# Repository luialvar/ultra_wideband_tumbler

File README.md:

# Tumbler UWB Subsystem Workspace

This repository organizes the hardware, mechanical-design, power-analysis, embedded-driver, and firmware material for the Tumbler UWB node in the AMADEE-27 university robotics project. The software migration from the older SKITH/DWM1000 platform to a newer STM32L4/DWM3000 PCB is a central part of the work, but it is not the whole project: the repository also captures the PCB, mechanical-integration, power-budget, and bring-up context needed to make the Tumbler subsystem usable.

The project is intentionally split by layer. The legacy folders are kept as engineering references, while the new CubeMX firmware and the Tumbler PCB are the active migration target.

## Project Context: AMADEE-27

This work was developed in the context of a university robotics project preparing a contribution for AMADEE-27, an international Mars analog mission managed by the Austrian Space Forum (OeWF).

AMADEE-27 is designed to emulate selected aspects of a human-robotic Mars mission. The mission concept combines analog astronauts, robotic systems, field experiments, and a Mission Support Center in Austria to recreate operational constraints similar to planetary exploration. The official AMADEE-27 call focuses on areas such as engineering and robotics, planetary surface operations, geoscience, life sciences, and human factors.

Within that broader university project, my responsibility was the Tumbler UWB subsystem rather than only a code port. That included understanding the old UWB localization stack, contributing to mechanical design and integration ideas, helping around the new PCB by studying the schematic/layout and matching it to firmware pin names, learning the practical hardware constraints, documenting the PCB and power-budget context, and preparing the new STM32CubeMX/HAL firmware structure for the upgraded PCB.

External context:

- Austrian Space Forum AMADEE-27 overview: https://oewf.org/en/amadee-27/
- AMADEE-27 Announcement of Opportunity: https://oewf.org/en/2025/12/amadee-27-ao/

## Tumbler Subsystem Scope

The important object in this repository is the Tumbler UWB subsystem as an integrated robot component. In practice, that means the work spans several connected areas:

- mechanical design exploration for fitting the electronics into the Tumbler concept,
- support and learning around the new PCB design, including how schematic/layout choices become firmware pin definitions,
- power-budget tracking for tag and anchor operating assumptions,
- low-level STM32L4/DWM3000 bring-up,
- migration of the old UWB ranging ideas onto a new CubeMX/HAL and Qorvo DW3xxx base.

The firmware migration is therefore one part of a larger embedded-system integration effort.

## Migration Summary

| Layer | Legacy platform | New platform |
| --- | --- | --- |
| Hardware | DWM1000-based SKITH board | DWM3000-based Tumbler board |
| Microcontroller | STM32F407 | STM32L431 |
| Framework | RODOS and legacy board wrappers | STM32Cube HAL generated by CubeMX |
| UWB driver | Decawave DWM1000 API | Qorvo DW3xxx driver |
| Application | Legacy tag/anchor ranging code | New CubeMX firmware for the new PCB |

## Repository Map

| Folder | Purpose |
| --- | --- |
| `SKITH_old_PCB/` | Legacy PCB design for the old SKITH UWB node. It represents the old hardware side of the DWM1000/STM32F407 platform. |
| `Tumbler_new_PCB/` | New PCB design for the upgraded UWB node. It contains the KiCad project, schematic sheets, layout, 3D exports, and production outputs for the DWM3000/STM32L431 board. |
| `power_calculations/` | Spreadsheet-based power budgets. The files are grouped around the old and new PCB assumptions, including anchor/tag operating modes. |
| `old_uwb_reference_repo/` | Legacy university toolkit component used as a software reference. It contains the old embedded DWM1000 firmware plus robot-side ROS localization code. |
| `software_new_pcb/` | New STM32CubeMX/HAL firmware for the new PCB. This is the active new-board software area. |
| `tumbler_images/` | Mechanical concept images and visual material for the Tumbler integration work. |
| `useful_links.txt` | Extra project links and references collected during development. |

## What Is Reused

The useful software inheritance is at the protocol level, not at the low-level driver level. The legacy code is valuable because it already contains the tag/anchor ranging flow, message types, timestamp packing, and two-way-ranging state machine. Those concepts can be ported to the new firmware.

The old Decawave DWM1000 driver, the RODOS scheduling code, the old SPI/GPIO wrappers, and the old board calibration constants should not be copied directly into the new STM32L431/DWM3000 firmware.

## Current Engineering Focus

The new firmware is built around STM32Cube HAL and the Qorvo DW3xxx driver. CubeMX describes the real wiring from the new PCB, including SPI, IRQ, reset, wakeup, power-control, and BMS-related pins. The firmware then uses those generated names in the board-port layer so that the UWB driver can talk to the DWM3000 through the actual hardware connections.

The practical bring-up path is:

1. Validate the CubeMX pin map against the Tumbler PCB schematic.
2. Bring up SPI, reset, wakeup, chip-select, and IRQ in the STM32 port layer.
3. Read the DW3xxx device ID through the Qorvo driver.
4. Test raw TX/RX frames.
5. Port the old tag/anchor ranging logic onto the new driver and HAL base.
6. Recalibrate antenna delays and timing for the new board.

## Engineering Highlights

This repository demonstrates a full embedded migration across hardware, firmware, and tooling boundaries:

- connecting mechanical integration constraints with the electronics layout,
- helping translate the new PCB design into a firmware-facing pin map,
- translating real PCB wiring into CubeMX/HAL pin definitions,
- replacing a legacy DWM1000 driver stack with the Qorvo DW3xxx driver,
- separating reusable ranging logic from non-reusable board/framework code,
- keeping only the required DW3xxx driver sources inside the firmware tree instead of storing the full vendor SDK,
- connecting firmware operating modes to spreadsheet-based power estimates.

## Notes for Reviewers

This repository is a migration and integration workspace, so it intentionally contains both original references and new implementation work. The separation is important: hardware design files document the boards, the power spreadsheets document expected operating modes, and the CubeMX firmware is where the new embedded software and DW3xxx driver integration are implemented.

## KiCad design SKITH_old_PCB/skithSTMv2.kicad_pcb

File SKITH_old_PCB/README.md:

# SKITH Old PCB

This folder contains the legacy PCB design for the older SKITH UWB node used as the starting point of the migration.

In the overall project, this is the old hardware reference:

| Layer | Value |
| --- | --- |
| UWB module | DWM1000 |
| Microcontroller family | STM32F407 |
| Firmware stack used with this board | RODOS, legacy wrappers, Decawave DWM1000 API |
| Role in this repository | Hardware reference for the legacy platform |

## Contents

| File or folder | Purpose |
| --- | --- |
| `skithSTMv2.kicad_pro` | KiCad project entry point. Open this file in KiCad to inspect the board. |
| `skithSTMv2.kicad_pcb` | PCB layout. |
| `skithSTMv2.sch` | Legacy schematic file. |
| `Schaltplan_Skith_STM_2.pdf` | PDF schematic export for quick review. |
| `skithSTMv2.brd` | Board file from the older design flow. |
| `sym-lib-table` | KiCad symbol-library configuration. |
| `skithSTMv2.kicad_dru` | KiCad design-rule settings. |
| `skithSTMv2.kicad_prl` | KiCad local/session state; useful for KiCad, but not part of the engineering design itself. |

## How This Fits the Migration

This board is not the firmware target for the new implementation. It is included so the old DWM1000/STM32F407 hardware can be compared against the new DWM3000/STM32L431 design.

The old firmware associated with this hardware is kept separately in `../old_uwb_reference_repo/embedded_uwb/`. The PCB files here describe the electrical design: connectors, MCU pins, UWB module wiring, power rails, and board layout.

For the new board, see `../Tumbler_new_PCB/`.

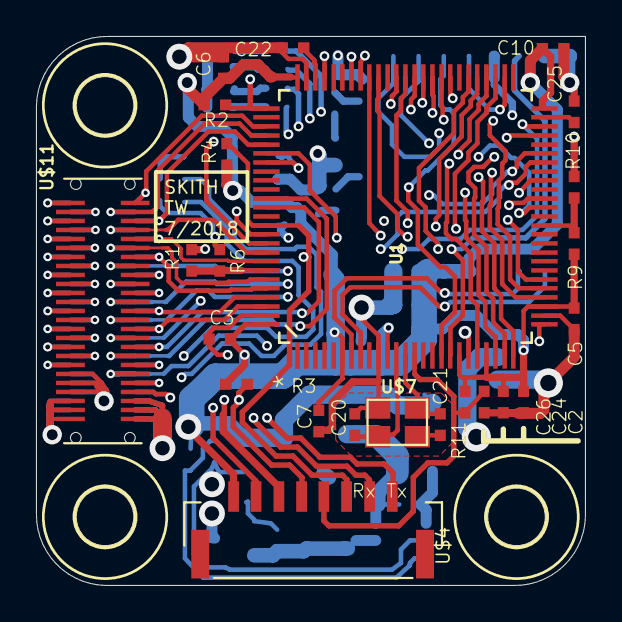
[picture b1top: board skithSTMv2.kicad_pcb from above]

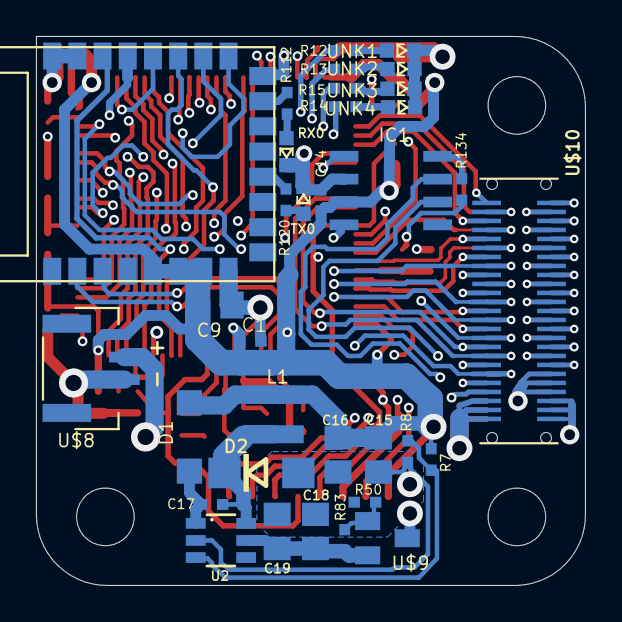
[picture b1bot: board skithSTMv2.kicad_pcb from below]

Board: 4 copper layers, 30.5 x 30.5 mm, 61 parts (34 on the bottom side), 79 nets.

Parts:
C1, C2, C3, C5, C6, C7, C10, C14, C17, C24, C26: 100n; C0402
C9, C15, C16, C18, C19: 10µ; C0805
C20, C21: 22p; C0402
C22, C25: 2,2µ; C0402
D1: 1N4148W-7-F; SOD123
D2: DO214AC
IC1: SN65HVD231D; SO8
L1: WE-TPC_2828
R1, R2, R3, R4, R6, R8, R9, R10, R11: 10k; R0402
R7: 31,6K; R0402
R12, R13, R14, R15, R112, R120, R134: 270; R0402
R50, R83: 1Meg; R0402
RX0: grün; SML0603
TX0: rot; SML0603
U1: STM32F407VGT6; QFP50P1600X1600X160-100N
U2: MCP16331; SOT23-6
U$1, U$5, U$6: 3,2
U$3: DWM1000
U$4: SM08B-GHS-TB
U$7: QC3CA16.0000F12B23M; LFXTAL055998
U$8: SM02B-GHS-TB
U$9: SI2369DS-T1-GE3; SOT23
U$10: DF12A-50DS-0.5V
U$11: DF12D(5.0)-50DP-0.5V
UNK1: grün; SML0603
UNK2: gelb; SML0603
UNK3: rot; SML0603
UNK4: blau; SML0603

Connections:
+3V3: C1.1, C2.1, C3.1, C5.1, C6.1, C7.1, C9.1, C10.1, C14.2, C15.1, C16.1, C24.1, D1.A, IC1.3, L1.2, R1.2, R2.2, R3.2, R4.1, R7.2, R9.2, R11.2, U1.6, U1.11, U1.19, U1.22, U1.28, U1.50, U1.75, U1.100, U$3.5, U$3.6, U$3.7, U$4.1, U$10.20, U$10.21, U$10.22, U$11.20, U$11.21, U$11.22
+24V: C18.1, C19.1, R83.2, U2.5, U$9.2
AD0: U1.23, U$10.8, U$11.8
AD1: U1.24, U$10.7, U$11.7
AD2: U1.25, U$10.6, U$11.6
AD3: U1.26, U$10.5, U$11.5
AD4: U1.29, U$10.4, U$11.4
AD5: U1.30, U$10.1, U$11.1
AD_REF: U1.21, U$10.2, U$11.2
BOOT1: R9.1, R10.2, U1.37
CAN1_RX: IC1.4, U1.81
CAN1_TX: IC1.1, U1.82
CAN_H: IC1.7, U$10.15, U$11.15
CAN_L: IC1.6, U$10.16, U$11.16
DEBUG_UART_RX: U1.69, U$4.7
DEBUG_UART_TX: U1.68, U$4.8
GND: C1.2, C2.2, C3.2, C5.2, C6.2, C7.2, C9.2, C10.2, C14.1, C15.2, C16.2, C18.2, C19.2, C20.2, C21.2, C22.2, C24.2, C25.2, C26.1, D2.A, IC1.2, R6.1, R8.1, R10.1, R50.1, R134.2, RX0.C, TX0.C, U1.10, U1.20, U1.27, U1.74, U1.99, U2.2, U$3.8, U$3.16, U$3.21, U$3.23, U$3.24, U$4.3, U$7.2, U$7.4, U$8.2, U$10.3, U$10.18, U$10.19, U$10.23, U$10.24, U$10.25, U$11.3, U$11.18, U$11.19, U$11.23, U$11.24, U$11.25, UNK1.C, UNK2.C, UNK3.C, UNK4.C
I2C_SCL: U1.47, U$10.17, U$11.17
I2C_SDA: U1.48, U$10.35, U$11.35
JTCK: R2.1, U1.76, U$4.2
JTMS: R3.1, U1.72, U$4.4
LED_BLAU: R12.2, U1.62
LED_GELB: R15.2, U1.60
LED_GRUEN: R14.2, U1.59
LED_ROT: R13.2, U1.61
unnamed: C22.1, U1.73
unnamed: R112.2, U$3.15
unnamed: R7.1, R8.2, U2.3
unnamed: C17.1, D1.C, U2.1
unnamed: C17.2, D2.C, L1.1, U2.6
unnamed: R12.1, UNK1.A
unnamed: R13.1, UNK2.A
unnamed: R14.1, UNK4.A
unnamed: R1.1, R6.2, U1.94
unnamed: R15.1, UNK3.A
unnamed: C25.1, U1.49
unnamed: IC1.8, R134.1
unnamed: R112.1, RX0.A
unnamed: R120.1, TX0.A
unnamed: R120.2, U$3.12
unnamed: R50.2, R83.1, U$9.1
NRST: C26.2, R11.1, U1.14, U$4.5
P0: U1.78, U$10.50, U$11.50
P1: U1.79, U$10.49, U$11.49
P2: U1.80, U$10.48, U$11.48
P3: U1.92, U$10.47, U$11.47
P4: U1.93, U$10.46, U$11.46
P5: U1.95, U$10.45, U$11.45
P6: U1.96, U$10.44, U$11.44
P7: U1.67, U$10.43, U$11.43
P8: U1.63, U$10.37, U$11.37
P9: U1.98, U$10.36, U$11.36
PH0: C20.1, U1.12, U$7.1
PH1: C21.1, U1.13, U$7.3
PWM0: U1.40, U$10.40, U$11.40
PWM1: U1.42, U$10.41, U$11.41
PWM2: U1.44, U$10.39, U$11.39
PWM3: U1.45, U$10.42, U$11.42
SPI0_CS0: U1.31, U$10.13, U$11.13
SPI0_CS1: U1.66, U$10.14, U$11.14
SPI0_CS2: U1.64, U$10.9, U$11.9
SPI0_CS3: U1.97, U$10.38, U$11.38
SPI0_MISO: U1.90, U$10.10, U$11.10
SPI0_MOSI: U1.91, U$10.11, U$11.11
SPI0_SCK/SWO: R4.2, U1.89, U$4.6, U$10.12, U$11.12
SPI_CS_DWM1000: U1.39, U$3.17
SPI_MISO_DWM1000: U1.17, U$3.19
SPI_MOSI_DWM1000: U1.54, U$3.18
SPI_SCK_DWM1000: U1.52, U$3.20
UART0_RX: U1.87, U$10.34, U$11.34
UART0_TX: U1.86, U$10.33, U$11.33
UART1_CTS: U1.58, U$10.29, U$11.29
UART1_RTS: U1.53, U$10.30, U$11.30
UART1_RX: U1.56, U$10.32, U$11.32
UART1_TX: U1.55, U$10.31, U$11.31
UWB_INT: U1.18, U$3.22
UWB_RESET: U1.7, U$3.3
UWB_WAKEUP: U1.8, U$3.2
V+: U$8.1, U$9.3, U$10.26, U$10.27, U$10.28, U$11.26, U$11.27, U$11.28

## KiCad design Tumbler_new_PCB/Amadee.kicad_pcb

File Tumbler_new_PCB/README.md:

# Tumbler New PCB

This folder contains the new PCB design for the upgraded UWB node. It is the hardware target for the STM32CubeMX/HAL firmware in `../software_new_pcb/`.

In the overall migration, this is the new hardware platform:

| Layer | Value |
| --- | --- |
| UWB module | DWM3000 family |
| Microcontroller | STM32L431 |
| Firmware stack | STM32Cube HAL plus Qorvo DW3xxx driver |
| Role in this repository | Active hardware target for the new firmware |

## Contents

| File or folder | Purpose |
| --- | --- |
| `Amadee.kicad_pro` | Main KiCad project entry point. Open this file first in KiCad. |
| `Amadee.kicad_sch` | Top-level schematic. |
| `mcu.kicad_sch` | Microcontroller schematic sheet. |
| `B2Bconn.kicad_sch` | Board-to-board connector sheet. |
| `bms.kicad_sch` | Battery-management subsystem sheet. |
| `buck.kicad_sch` | Buck-regulator/power-conversion sheet. |
| `usb.kicad_sch` | USB-related circuitry. |
| `back-to-back-fets.kicad_sch` | Power-path/protection FET sheet. |
| `Amadee.kicad_pcb` | PCB layout. |
| `AmadeeTumbler.step` | 3D mechanical export for CAD review. |
| `AmadeeTumbler.stl` | 3D mesh export. |
| `AmadeeTumbler.pdf` | PDF design export for quick review. |
| `production/` | Manufacturing outputs. |
| `PowerCalc/` | Power-calculation spreadsheets colocated with the PCB project. |
| `lib/` | KiCad footprint/library assets used by the board. |

## Firmware-Relevant Signals

The PCB defines the real electrical wiring. CubeMX must mirror that wiring so the firmware can use the correct MCU pins for:

| Signal group | Why it matters in firmware |
| --- | --- |
| SPI | Data path between the STM32L431 and the DWM3000. |
| Chip select | Selects the UWB chip during SPI transactions. |
| IRQ | Lets the DWM3000 notify the MCU about TX/RX events. |
| Reset | Allows the MCU to reset the UWB module during bring-up. |
| Wakeup | Lets the MCU bring the UWB module out of low-power states. |
| Power and BMS pins | Control and monitor board power behavior. |

This is why the PCB and CubeMX project must agree. The PCB is the physical truth; CubeMX translates that physical wiring into generated C names used by the HAL and by the Qorvo driver port layer.

## Relationship to the Old PCB

The old `../SKITH_old_PCB/` design represents the DWM1000/STM32F407 generation. This folder represents the DWM3000/STM32L431 generation.

The migration is therefore not just a source-code copy. It changes the radio module, the MCU, the framework, the low-level driver, and the board pinout.

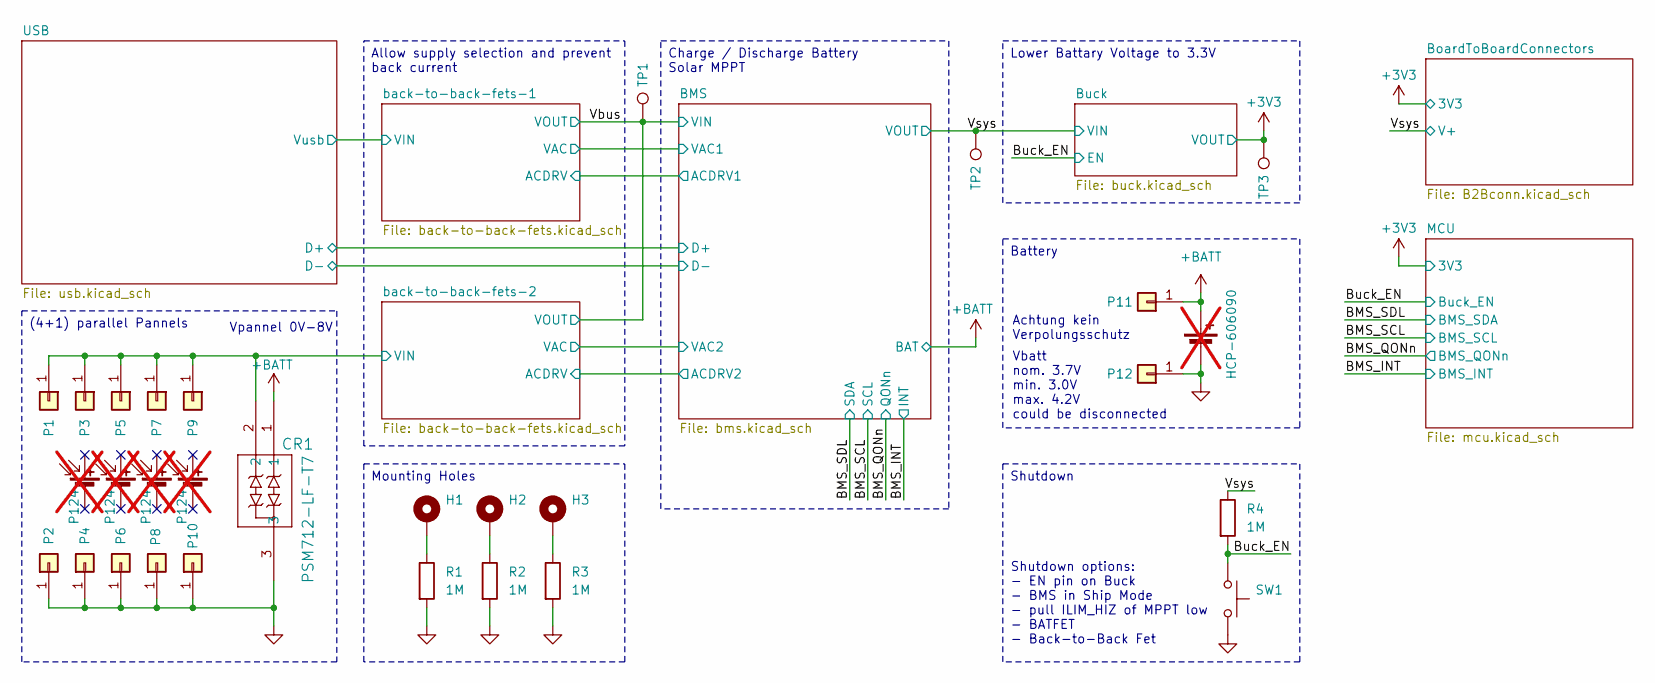
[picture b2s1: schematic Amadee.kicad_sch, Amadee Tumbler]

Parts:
BT1: HCP-606090; not fitted
CR1: PSM712-LF-T7; CR_SOT-23_PTD; LCSC C32677
H1, H2, H3: MountingHole_Pad; MountingHole_3.2mm_M3_DIN965_Pad
P1, P2, P3, P4, P5, P6, P7, P8, P9, P10, P11, P12: SolderPad_4mm_2mm
R1, R2, R3: 1M; R_0603_1608Metric_Pad0.98x0.95mm_HandSolder
R4: 1M; R_0402_1005Metric_Pad0.72x0.64mm_HandSolder
SC1, SC2, SC3, SC4: P124; not fitted
SW1: SW_Push; SW_SPST_TS-1088-xR020; LCSC C720477
TP1, TP2, TP3: TestPoint; TestPoint_Pad_D1.5mm

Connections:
+3V3: TP3.1 (1_1); also elsewhere on the board
+BATT: BT1.1 (+), CR1.1, P11.1 (Pin_1_1); also elsewhere on the board
/BMS/VAC2: CR1.2, P1.1 (Pin_1_1), P3.1 (Pin_1_1), P5.1 (Pin_1_1), P7.1 (Pin_1_1), P9.1 (Pin_1_1); also elsewhere on the board
/Buck_EN: R4.2, SW1.1; also elsewhere on the board
/Vbus: TP1.1 (1_1); also elsewhere on the board
/Vsys: R4.1, TP2.1 (1_1); also elsewhere on the board
GND: BT1.2 (-), CR1.3, P2.1 (Pin_1_1), P4.1 (Pin_1_1), P6.1 (Pin_1_1), P8.1 (Pin_1_1), P10.1 (Pin_1_1), P12.1 (Pin_1_1), R1.2, R2.2, R3.2, SW1.2; also elsewhere on the board
unnamed: H1.1 (1_1), R1.1
unnamed: H2.1 (1_1), R2.1
unnamed: H3.1 (1_1), R3.1

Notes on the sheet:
Vpannel 0V-8V
Vbatt nom. 3.7V min. 3.0V max. 4.2V could be disconnected
Shutdown options: - EN pin on Buck - BMS in Ship Mode - pull ILIM_HIZ of MPPT low - BATFET - Back-to-Back Fet
Achtung kein Verpolungsschutz
Battery
Lower Battary Voltage to 3.3V
Charge / Discharge Battery Solar MPPT
Shutdown
Allow supply selection and prevent back current
(4+1) parallel Pannels
Mounting Holes

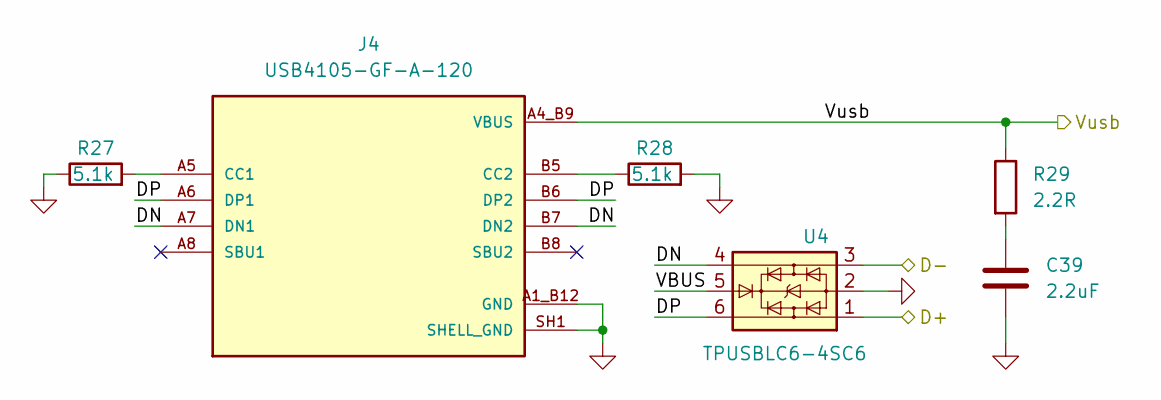
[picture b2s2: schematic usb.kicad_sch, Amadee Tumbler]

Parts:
C39: 2.2uF; C_0805_2012Metric_Pad1.18x1.45mm_HandSolder
J4: USB4105-GF-A-120; GCT_USB4105-GF-A-120; PARTREV B3; LCSC C5184243
R27, R28: 5.1k; R_0603_1608Metric_Pad0.98x0.95mm_HandSolder
R29: 2.2R; R_0603_1608Metric_Pad0.98x0.95mm_HandSolder
U4: TPUSBLC6-4SC6; SOT-23-6; LCSC C558419

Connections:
/BMS/D+: U4.1; also elsewhere on the board
/BMS/D-: U4.3; also elsewhere on the board
/USB/DN: J4.A7 (DN1), J4.B7 (DN2), U4.4
/USB/DP: J4.A6 (DP1), J4.B6 (DP2), U4.6
GND: C39.2, J4.A1_B12 (GND), J4.B1_A12 (GND), J4.SH1 (SHELL_GND), J4.SH2 (SHELL_GND), J4.SH3 (SHELL_GND), J4.SH4 (SHELL_GND), R27.1, R28.2, U4.2; also elsewhere on the board
unnamed: C39.1, R29.2
unnamed: J4.A5 (CC1), R27.2
unnamed: J4.B5 (CC2), R28.1
VBUS: J4.A4_B9 (VBUS), J4.B4_A9 (VBUS), R29.1, U4.5; also elsewhere on the board

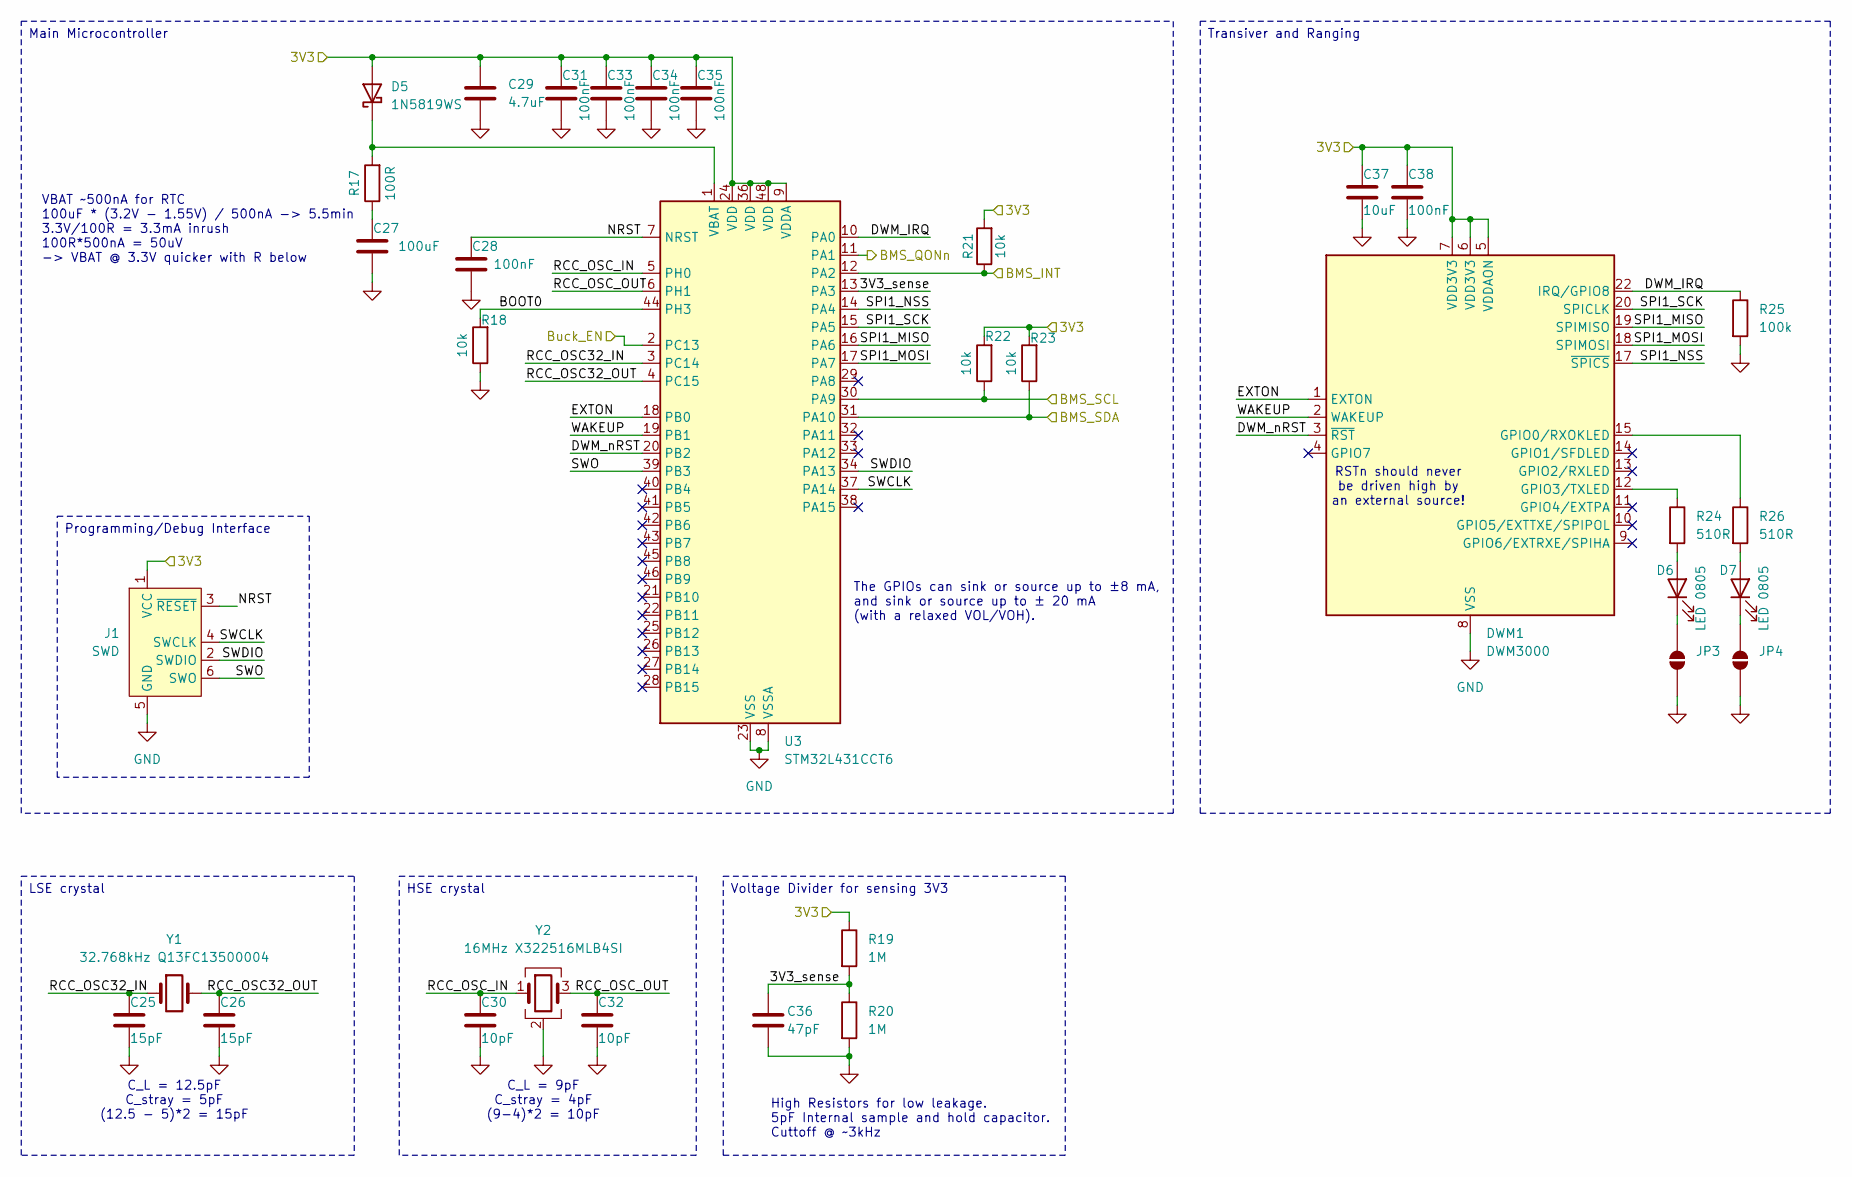
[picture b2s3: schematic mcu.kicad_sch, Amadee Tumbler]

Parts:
C25, C26: 15pF; C_0402_1005Metric
C27: 100uF; C_1206_3216Metric
C28, C31, C33, C34, C35, C38: 100nF; C_0402_1005Metric_Pad0.74x0.62mm_HandSolder
C29: 4.7uF; C_0805_2012Metric_Pad1.18x1.45mm_HandSolder
C30, C32: 10pF; C_0402_1005Metric
C36: 47pF; C_0402_1005Metric_Pad0.74x0.62mm_HandSolder
C37: 10uF; C_0402_1005Metric_Pad0.74x0.62mm_HandSolder
D5: 1N5819WS; D_SOD-323
D6, D7: LED 0805; LED_0805_2012Metric_Pad1.15x1.40mm_HandSolder; LCSC C2296
DWM1: DWM3000; DWM1000; LCSC C42419011
J1: SWD; PinHeader_2x03_P2.54mm_Vertical_SMD; LCSC C192301
JP3, JP4: SolderJumper_2_Open; SolderJumper-2_P1.3mm_Open_RoundedPad1.0x1.5mm
R17: 100R; R_0402_1005Metric_Pad0.72x0.64mm_HandSolder
R18, R21, R22, R23: 10k; R_0402_1005Metric_Pad0.72x0.64mm_HandSolder
R19, R20: 1M; R_0402_1005Metric_Pad0.72x0.64mm_HandSolder
R24, R26: 510R; R_0402_1005Metric_Pad0.72x0.64mm_HandSolder
R25: 100k; R_0402_1005Metric_Pad0.72x0.64mm_HandSolder
U3: STM32L431CCT6; LQFP-48_7x7mm_P0.5mm; LCSC C486681
Y1: 32.768kHz Q13FC13500004; Crystal_SMD_3215-2Pin_3.2x1.5mm; LCSC C32346
Y2: 16MHz X322516MLB4SI; Crystal_SMD_3225-4Pin_3.2x2.5mm; LCSC C13738

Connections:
+3V3: C29.1, C31.1, C33.1, C34.1, C35.1, C37.1, C38.1, D5.2 (A), DWM1.5 (VDDAON), DWM1.6 (VDD3V3), DWM1.7 (VDD3V3), J1.1 (VCC), R19.1, R21.2, R22.2, R23.2, U3.9 (VDDA), U3.24 (VDD), U3.36 (VDD), U3.48 (VDD); also elsewhere on the board
/BMS_INT: R21.1, U3.12 (PA2); also elsewhere on the board
/BMS_QONn: U3.11 (PA1); also elsewhere on the board
/BMS_SCL: R22.1, U3.30 (PA9); also elsewhere on the board
/BMS_SDL: R23.1, U3.31 (PA10); also elsewhere on the board
/Buck_EN: U3.2 (PC13); also elsewhere on the board
/MCU/3V3_sense: C36.1, R19.2, R20.1, U3.13 (PA3)
/MCU/BOOT0: R18.2, U3.44 (PH3)
/MCU/DWM_IRQ: DWM1.22 (IRQ/GPIO8), R25.1, U3.10 (PA0)
/MCU/DWM_nRST: DWM1.3 (~RST), U3.20 (PB2)
/MCU/EXTON: DWM1.1 (EXTON), U3.18 (PB0)
/MCU/NRST: C28.1, J1.3 (~RESET), U3.7 (NRST)
/MCU/RCC_OSC32_IN: C25.1, U3.3 (PC14), Y1.1
/MCU/RCC_OSC32_OUT: C26.1, U3.4 (PC15), Y1.2
/MCU/RCC_OSC_IN: C30.1, U3.5 (PH0), Y2.1
/MCU/RCC_OSC_OUT: C32.1, U3.6 (PH1), Y2.3
/MCU/SPI1_MISO: DWM1.19 (SPIMISO), U3.16 (PA6)
/MCU/SPI1_MOSI: DWM1.18 (SPIMOSI), U3.17 (PA7)
/MCU/SPI1_NSS: DWM1.17 (~SPICS), U3.14 (PA4)
/MCU/SPI1_SCK: DWM1.20 (SPICLK), U3.15 (PA5)
/MCU/SWCLK: J1.4 (SWCLK), U3.37 (PA14)
/MCU/SWDIO: J1.2 (SWDIO), U3.34 (PA13)
/MCU/SWO: J1.6 (SWO), U3.39 (PB3)
/MCU/WAKEUP: DWM1.2 (WAKEUP), U3.19 (PB1)
GND: C25.2, C26.2, C27.2, C28.2, C29.2, C30.2, C31.2, C32.2, C33.2, C34.2, C35.2, C36.2, C37.2, C38.2, DWM1.8 (VSS), DWM1.16 (VSS), DWM1.21 (VSS), DWM1.23 (VSS), DWM1.24 (VSS), J1.5 (GND), JP3.1 (A), JP4.1 (A), R18.1, R20.2, R25.2, U3.8 (VSSA), U3.23 (VSS), U3.35 (VSS), U3.47 (VSS), Y2.2 (G), Y2.4 (G); also elsewhere on the board
unnamed: C27.1, R17.1
unnamed: D5.1 (K), R17.2, U3.1 (VBAT)
unnamed: D6.2 (A), R24.2
unnamed: D6.1 (K), JP3.2 (B)
unnamed: D7.2 (A), R26.2
unnamed: D7.1 (K), JP4.2 (B)
unnamed: DWM1.15 (GPIO0/RXOKLED), R26.1
unnamed: DWM1.12 (GPIO3/TXLED), R24.1

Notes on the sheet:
VBAT ~500nA for RTC 100uF * (3.2V - 1.55V) / 500nA -> 5.5min 3.3V/100R = 3.3mA inrush 100R*500nA = 50uV -> VBAT @ 3.3V quicker with R below
The GPIOs can sink or source up to ±8 mA, and sink or source up to ± 20 mA (with a relaxed VOL/VOH).
C_L = 12.5pF C_stray = 5pF (12.5 - 5)*2 = 15pF
C_L = 9pF C_stray = 4pF (9-4)*2 = 10pF
High Resistors for low leakage. 5pF Internal sample and hold capacitor. Cuttoff @ ~3kHz
RSTn should never be driven high by an external source!
HSE crystal
Voltage Divider for sensing 3V3
Transiver and Ranging
LSE crystal
Main Microcontroller
Programming/Debug Interface

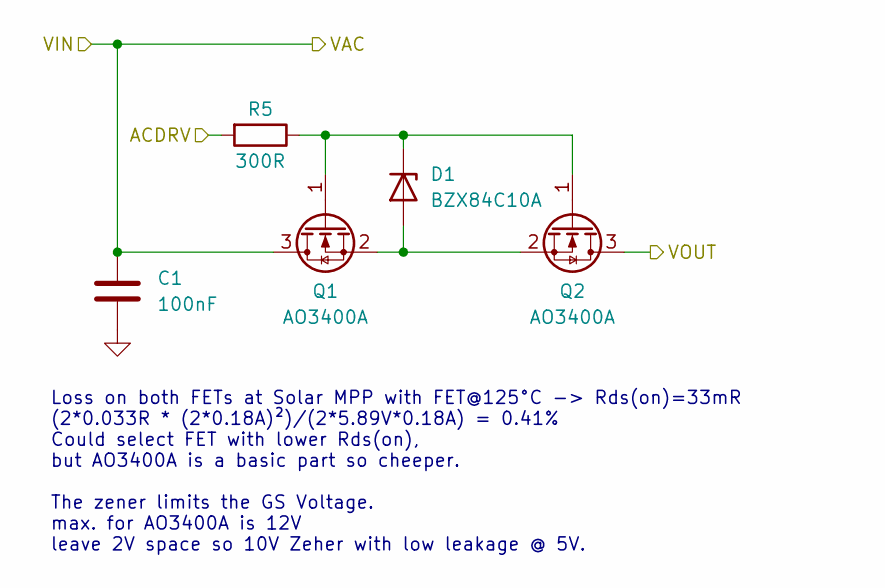
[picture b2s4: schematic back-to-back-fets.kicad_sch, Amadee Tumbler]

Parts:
C1: 100nF; C_0402_1005Metric_Pad0.74x0.62mm_HandSolder
D1: BZX84C10A; SOT-23; LCSC C5155278
Q1, Q2: AO3400A; SOT-23; LCSC C20917
R5: 300R; R_0402_1005Metric_Pad0.72x0.64mm_HandSolder

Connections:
/BMS/ACDRV1: R5.2; also elsewhere on the board
/Vbus: Q2.3 (D); also elsewhere on the board
GND: C1.2; also elsewhere on the board
unnamed: D1.1 (A), Q1.2 (S), Q2.2 (S)
unnamed: D1.3 (K), Q1.1 (G), Q2.1 (G), R5.1
VBUS: C1.1, Q1.3 (D); also elsewhere on the board

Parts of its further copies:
C2: 100nF; C_0402_1005Metric_Pad0.74x0.62mm_HandSolder
D2: BZX84C10A; SOT-23; LCSC C5155278
Q3, Q4: AO3400A; SOT-23; LCSC C20917
R6: 300R; R_0402_1005Metric_Pad0.72x0.64mm_HandSolder

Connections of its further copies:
/BMS/ACDRV2: R6.2; also elsewhere on the board
/BMS/VAC2: C2.1, Q3.3 (D); also elsewhere on the board
/Vbus: Q4.3 (D); also elsewhere on the board
GND: C2.2; also elsewhere on the board
unnamed: D2.1 (A), Q3.2 (S), Q4.2 (S)
unnamed: D2.3 (K), Q3.1 (G), Q4.1 (G), R6.1

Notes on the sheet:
Loss on both FETs at Solar MPP with FET@125°C -> Rds(on)=33mR (2*0.033R * (2*0.18A)²)/(2*5.89V*0.18A) = 0.41% Could select FET with lower Rds(on), but AO3400A is a basic part so cheeper. The zener limits the GS Voltage. max. for AO3400A is 12V leave 2V space so 10V Zeher with low leakage @ 5V.

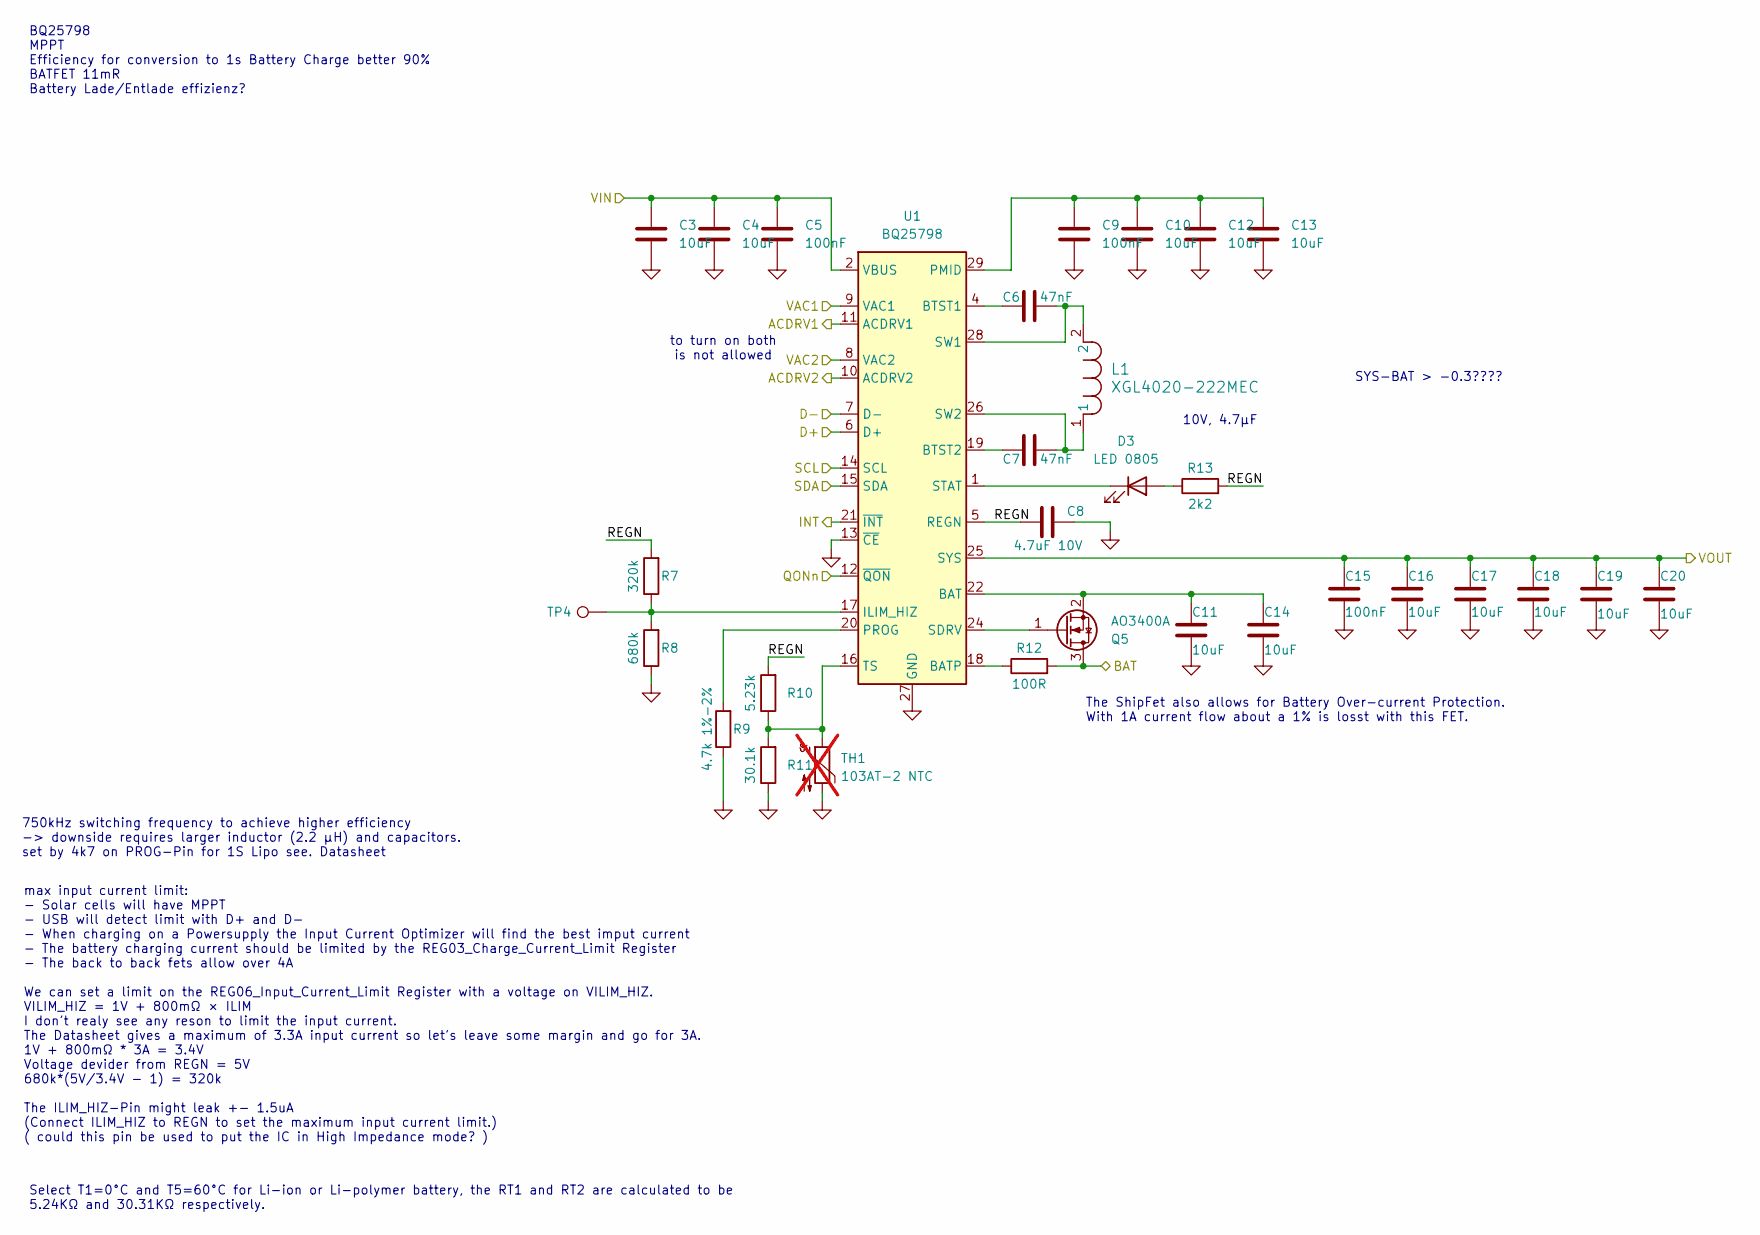
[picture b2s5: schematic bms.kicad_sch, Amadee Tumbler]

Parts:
C3, C4, C10, C11, C12, C13, C14, C16, C17, C18, C19, C20: 10uF; C_0402_1005Metric_Pad0.74x0.62mm_HandSolder
C5, C9, C15: 100nF; C_0402_1005Metric_Pad0.74x0.62mm_HandSolder
C6, C7: 47nF; C_0402_1005Metric_Pad0.74x0.62mm_HandSolder
C8: 4.7uF 10V; C_0402_1005Metric_Pad0.74x0.62mm_HandSolder
D3: LED 0805; LED_0805_2012Metric_Pad1.15x1.40mm_HandSolder; LCSC C2296
L1: XGL4020-222MEC; IND_XGL4020_COC
Q5: AO3400A; SOT-23; LCSC C20917
R7: 320k; R_0402_1005Metric_Pad0.72x0.64mm_HandSolder
R8: 680k; R_0402_1005Metric_Pad0.72x0.64mm_HandSolder
R9: 4.7k 1%-2%; R_0402_1005Metric_Pad0.72x0.64mm_HandSolder
R10: 5.23k; R_0402_1005Metric_Pad0.72x0.64mm_HandSolder
R11: 30.1k; R_0402_1005Metric_Pad0.72x0.64mm_HandSolder
R12: 100R; R_0402_1005Metric_Pad0.72x0.64mm_HandSolder
R13: 2k2; R_0402_1005Metric_Pad0.72x0.64mm_HandSolder
TH1: 103AT-2 NTC; PinHeader_1x02_P2.54mm_Vertical; not fitted
TP4: TestPoint; TestPoint_Pad_D1.0mm
U1: BQ25798; Texas_RQM0029A_VQFN-29_4x4mm_P0.4mm

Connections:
+BATT: Q5.3 (D), R12.2; also elsewhere on the board
/BMS/ACDRV1: U1.11 (ACDRV1); also elsewhere on the board
/BMS/ACDRV2: U1.10 (ACDRV2); also elsewhere on the board
/BMS/D+: U1.6 (D+); also elsewhere on the board
/BMS/D-: U1.7 (D-); also elsewhere on the board
/BMS/REGN: C8.1, R7.2, R10.2, R13.2, U1.5 (REGN)
/BMS/VAC2: U1.8 (VAC2); also elsewhere on the board
/BMS_INT: U1.21 (~INT); also elsewhere on the board
/BMS_QONn: U1.12 (~QON); also elsewhere on the board
/BMS_SCL: U1.14 (SCL); also elsewhere on the board
/BMS_SDL: U1.15 (SDA); also elsewhere on the board
/Vbus: C3.1, C4.1, C5.1, U1.2 (VBUS), U1.3 (VBUS); also elsewhere on the board
/Vsys: C15.1, C16.1, C17.1, C18.1, C19.1, C20.1, U1.25 (SYS); also elsewhere on the board
GND: C3.2, C4.2, C5.2, C8.2, C9.2, C10.2, C11.2, C12.2, C13.2, C14.2, C15.2, C16.2, C17.2, C18.2, C19.2, C20.2, R8.1, R9.1, R11.1, TH1.2, U1.13 (~CE), U1.27 (GND); also elsewhere on the board
unnamed: D3.2 (A), R13.1
unnamed: D3.1 (K), U1.1 (STAT)
unnamed: Q5.1 (G), U1.24 (SDRV)
unnamed: C11.1, C14.1, Q5.2 (S), U1.22 (BAT), U1.23 (BAT)
unnamed: R12.1, U1.18 (BATP)
unnamed: C6.1, U1.4 (BTST1)
unnamed: C7.1, U1.19 (BTST2)
unnamed: R7.1, R8.2, TP4.1 (1_1), U1.17 (ILIM_HIZ)
unnamed: C9.1, C10.1, C12.1, C13.1, U1.29 (PMID)
unnamed: R9.2, U1.20 (PROG)
unnamed: C6.2, L1.2, U1.28 (SW1)
unnamed: C7.2, L1.1, U1.26 (SW2)
unnamed: R10.1, R11.2, TH1.1, U1.16 (TS)
VBUS: U1.9 (VAC1); also elsewhere on the board

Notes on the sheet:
SYS-BAT > -0.3????
The ShipFet also allows for Battery Over-current Protection. With 1A current flow about a 1% is losst with this FET.
max input current limit: - Solar cells will have MPPT - USB will detect limit with D+ and D- - When charging on a Powersupply the Input Current Optimizer will find the best imput current - The battery charging current should be limited by the REG03_Charge_Current_Limit Register - The back to back f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
BQ25798 MPPT Efficiency for conversion to 1s Battery Charge better 90% BATFET 11mR Battery Lade/Entlade effizienz?
10V, 4.7μF
Select T1=0°C and T5=60°C for Li-ion or Li-polymer battery, the RT1 and RT2 are calculated to be 5.24KΩ and 30.31KΩ respectively.
750kHz switching frequency to achieve higher efficiency -> downside requires larger inductor (2.2 μH) and capacitors. set by 4k7 on PROG-Pin for 1S Lipo see. Datasheet
to turn on both is not allowed

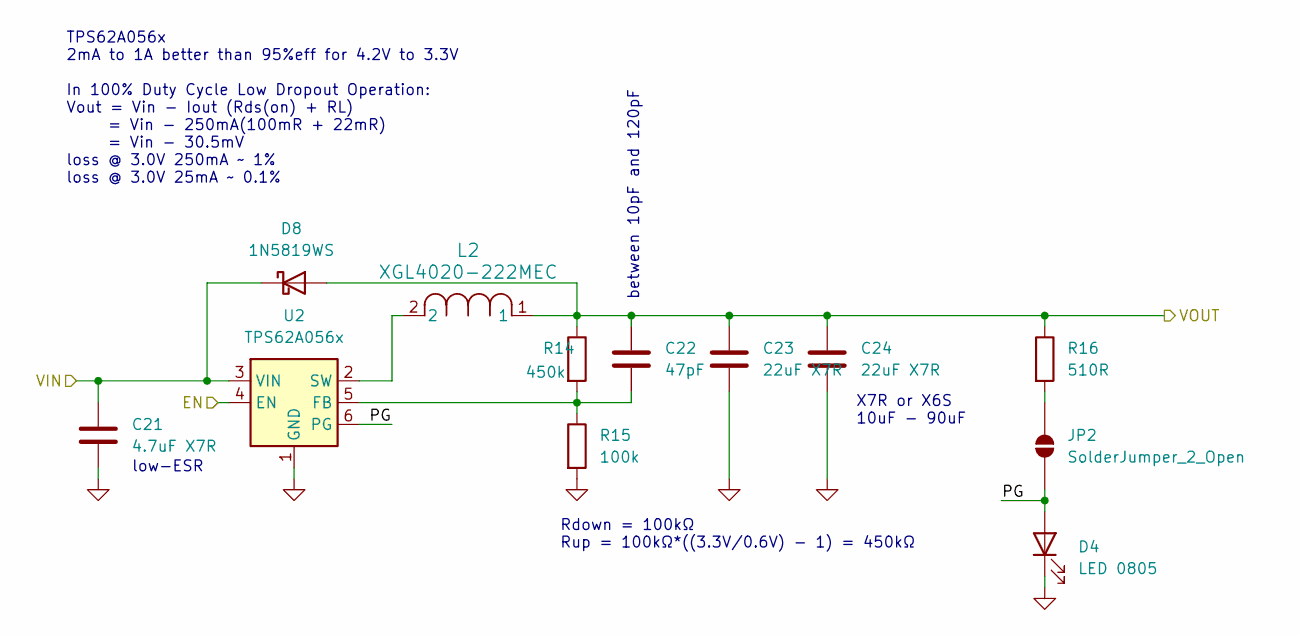
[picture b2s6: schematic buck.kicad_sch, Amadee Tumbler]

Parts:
C21: 4.7uF X7R; C_0805_2012Metric_Pad1.18x1.45mm_HandSolder; LCSC C49678
C22: 47pF; C_0402_1005Metric_Pad0.74x0.62mm_HandSolder
C23, C24: 22uF X7R; C_0805_2012Metric_Pad1.18x1.45mm_HandSolder
D4: LED 0805; LED_0805_2012Metric_Pad1.15x1.40mm_HandSolder; LCSC C2296
D8: 1N5819WS; D_SOD-323
JP2: SolderJumper_2_Open; SolderJumper-2_P1.3mm_Open_RoundedPad1.0x1.5mm
L2: XGL4020-222MEC; IND_XGL4020_COC
R14: 450k; R_0402_1005Metric_Pad0.72x0.64mm_HandSolder
R15: 100k; R_0402_1005Metric_Pad0.72x0.64mm_HandSolder
R16: 510R; R_0402_1005Metric_Pad0.72x0.64mm_HandSolder
U2: TPS62A056x; SOT-563

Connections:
+3V3: C22.1, C23.1, C24.1, D8.2 (A), L2.1, R14.1, R16.1; also elsewhere on the board
/Buck/PG: D4.2 (A), JP2.1 (A), U2.6 (PG)
/Buck_EN: U2.4 (EN); also elsewhere on the board
/Vsys: C21.1, D8.1 (K), U2.3 (VIN); also elsewhere on the board
GND: C21.2, C23.2, C24.2, D4.1 (K), R15.2, U2.1 (GND); also elsewhere on the board
unnamed: JP2.2 (B), R16.2
unnamed: C22.2, R14.2, R15.1, U2.5 (FB)
unnamed: L2.2, U2.2 (SW)

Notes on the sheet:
Rdown = 100kΩ Rup = 100kΩ*((3.3V/0.6V) - 1) = 450kΩ
low-ESR
TPS62A056x 2mA to 1A better than 95%eff for 4.2V to 3.3V In 100% Duty Cycle Low Dropout Operation: Vout = Vin - Iout (Rds(on) + RL) = Vin - 250mA(100mR + 22mR) = Vin - 30.5mV loss @ 3.0V 250mA ~ 1% loss @ 3.0V 25mA ~ 0.1%
between 10pF and 120pF
X7R or X6S 10uF - 90uF

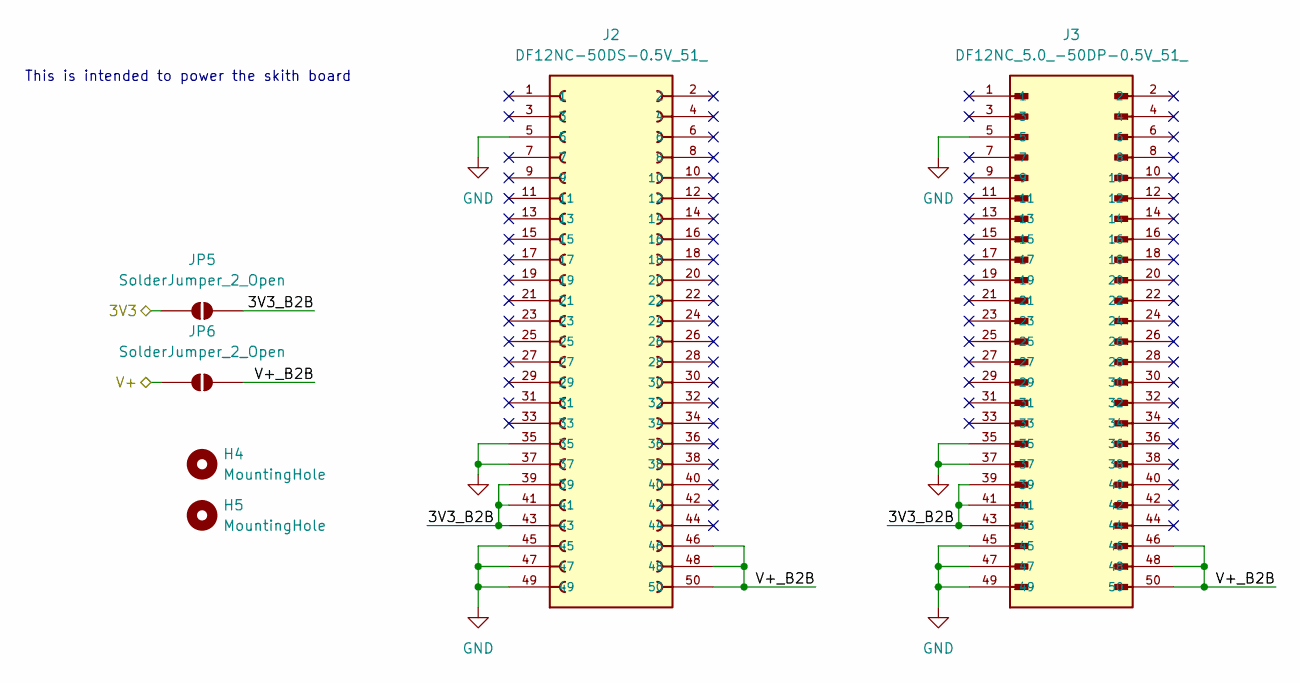
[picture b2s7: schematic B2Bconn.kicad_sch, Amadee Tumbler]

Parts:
H4, H5: MountingHole; MountingHole_3.2mm_M3_DIN965
J2: DF12NC-50DS-0.5V_51_; HRS_DF12NC-50DS-0.5V_51_; DigiKey_Part_Number 26-DF12NC-50DS-0.5V(51)CT-ND
J3: DF12NC_5.0_-50DP-0.5V_51_; HRS_DF12NC_5.0_-50DP-0.5V_51_; DigiKey_Part_Number 26-DF12NC(5.0)-50DP-0.5V(51)CT-ND
JP5, JP6: SolderJumper_2_Open; SolderJumper-2_P1.3mm_Open_RoundedPad1.0x1.5mm

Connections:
+3V3: JP5.2 (B); also elsewhere on the board
/BoardToBoardConnectors/3V3_B2B: J2.39, J2.41, J2.43, J3.39, J3.41, J3.43, JP5.1 (A)
/BoardToBoardConnectors/V+_B2B: J2.46, J2.48, J2.50, J3.46, J3.48, J3.50, JP6.1 (A)
/Vsys: JP6.2 (B); also elsewhere on the board
GND: J2.5, J2.35, J2.37, J2.45, J2.47, J2.49, J3.5, J3.35, J3.37, J3.45, J3.47, J3.49; also elsewhere on the board

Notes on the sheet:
This is intended to power the skith board
